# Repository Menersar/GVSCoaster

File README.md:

<!-- PROJECT LOGO -->
<br />
<div align="center">

<h3 align="center">GVS Coaster</h3>

</div>

<!-- TABLE OF CONTENTS -->
<details>
  <summary>Table of Contents</summary>
  <ol>
    <li>
      <a href="#respository-structure">Respository Structure</a>
    </li>
    <li>
      <a href="#setup-for-mqtt-connection-for-the-galvanic-vestibular-stimulation-gvs">Setup for MQTT Connection</a>
    </li>
  </ol>
</details>

## Respository Structure

### Build (Android APK):
- Found under \Build.

### Documentation and Video:
- Found under \Documentation.

### Unity project files:
- Found under \Sources\Unity.

### Arduino (ESP) files:
- Found under \Sources\Arduino.

### Libraries used for the Arduino (ESP) project:
- Found under \Sources\Arduino\libraries.
- To use them, copy these into folder C:\Users\USERNAME\Documents\Arduino\libraries.

### Eagle Schematic and Board:
- Found under \Sources\Eagle.

## Setup for MQTT Connection (for the Galvanic Vestibular Stimulation (GVS))

### Required (for connection with local MQTT-Broker): 
- Install Mosquitto MQTT broker on a local PC (found under \Sources\_Mosquitto MQTT Broker).
- Replace the "mosquitto.conf" in the mosquitto installation folder with the "mosquitto.conf" file (found under \Sources\_MosquittoMQTTBroker).
- Run the Command Prompt as administrator and type "net start mosquitto" to start the mosquitto MQTT broker locally ("net stop mosquitto" to stop).

### Nice to have for monitoring of the MQTT messages:
- Install MQTT.fx (found under \Sources\_MQTTFx).
- Click on the options icon, if installed on the same computer as the MQTT broker, set the Broker Adress to "127.0.0.1" and the Port to "1883".
- Click on Connect.
- Now you are able to Subscribe and Publish to Topics.
- For this project the two topics used are "M2MQTT_Unity/test/ESPXY/outTopic" (messages from the ESP) and "M2MQTT_Unity/test/ESPXY/inTopic" (messages from Unity / the application).

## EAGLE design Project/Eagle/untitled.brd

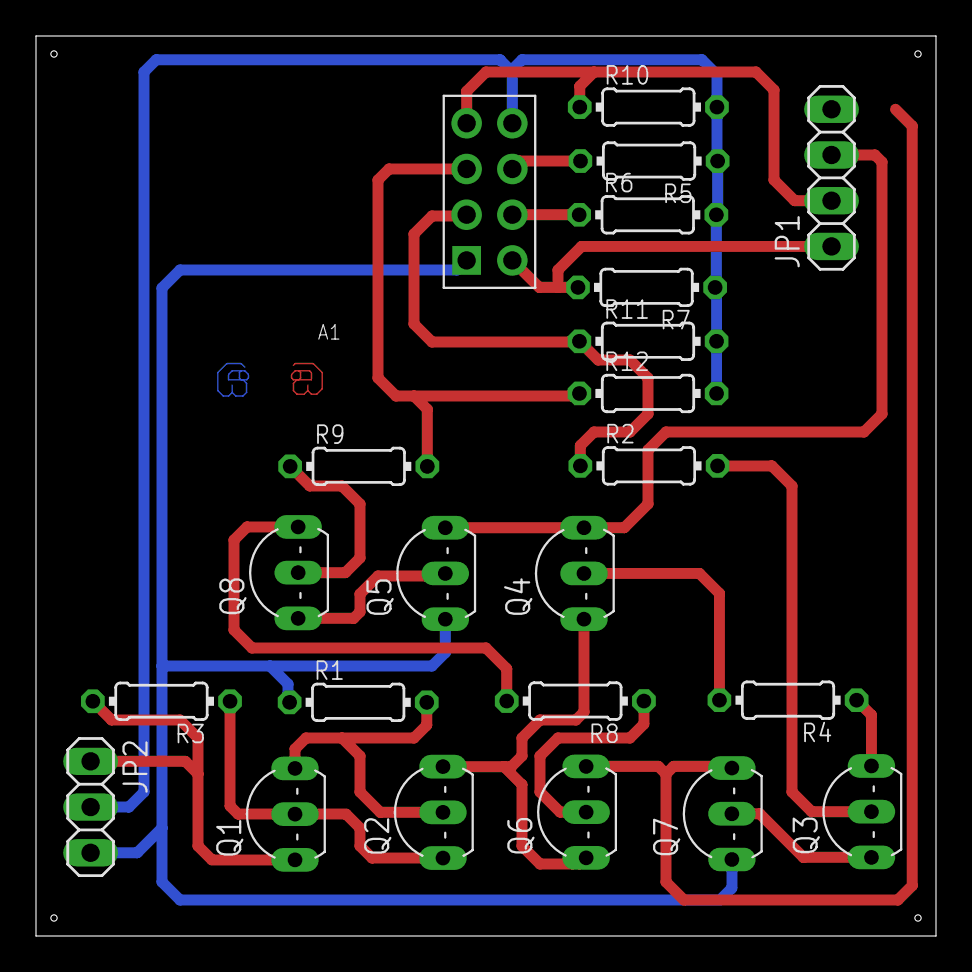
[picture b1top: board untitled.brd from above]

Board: 2 copper layers, 50.0 x 50.0 mm, 23 parts (0 on the bottom side), 22 nets.

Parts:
A1: ESP8266_ESP-01_NO-SILKSCREEN
JP1: 1X04
JP2: 1X03
Q1, Q2, Q4, Q6: 2N3906; TO92-EBC
Q3, Q5, Q7, Q8: 2N3904; TO92-EBC
R1, R5, R6, R7, R10, R11, R12: 5,6k; 0204/7
R2, R9: 1,8k; 0204/7
R3: 220; 0204/7
R4, R8: 12k; 0204/7

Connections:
GND: A1.GND, JP2.3, Q5.E, Q7.E, R1.1
unnamed: A1.RST, R5.2
unnamed: A1.EN/CH_PD, R6.1
unnamed: A1.RX, JP1.2, R10.1
unnamed: A1.GPIO0, R9.2, R12.1
unnamed: Q3.B, R2.2
unnamed: Q3.C, R4.1
unnamed: Q4.B, R4.2
unnamed: Q2.C, Q4.E, Q6.E
unnamed: Q1.C, Q2.B, R1.2
unnamed: JP1.3, Q4.C, Q5.C
unnamed: JP2.1, Q1.E, R3.2
unnamed: Q1.B, Q2.E, R3.1
unnamed: JP1.4, Q6.C, Q7.C
unnamed: Q6.B, R8.1
unnamed: Q3.E, Q7.B
unnamed: Q8.C, R8.2
unnamed: Q5.B, Q8.E
unnamed: Q8.B, R9.1
unnamed: A1.GPIO2, R2.1, R11.1
unnamed: A1.TX, JP1.1, R7.2
VCC: A1.3V3, JP2.2, R5.1, R6.2, R7.1, R10.2, R11.2, R12.2

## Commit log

2022-02-10 uploaded all current project files
2022-02-10 renamed folder
2022-02-16 added unity2
2022-02-17 added environment and beginning of settings
2022-02-19 finished options, fixed bugs, changed visuals
2022-02-19 changed visuals, added exit functionality, fixed bugs
2022-02-24 vr10
2022-02-26 deleted old project
2022-02-26 new version uploaded
2022-02-26 added safe functionality for wlan password and ssid
2022-02-26 updated repository
2022-02-26 added apk
2022-02-27 added documentations and build and updated unity project
2022-02-28 added matrikelnummer to documentation
2022-02-28 Abgabe
2022-03-15 v2 Unity
